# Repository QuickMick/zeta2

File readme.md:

streaming:
https://www.npmjs.com/package/h264-live-player
https://github.com/131/h264-live-player

old:https://www.npmjs.com/package/raspivid-stream

fan: 0.33 a
GY-88: 0.3 mA

pin input draw (zero position): 0.1 mA

kaufen:IRLML2502
schalter
lötsinn
kabel?
kondensator 47uf, 4.7uf 10uf
0.1uf
470uf
steckbrett

stepper: min 47uf

vllt au den:
IRF3708

crompzange

---------old----------

S8550 -< PNP
https://alltransistors.com/transistor.php?transistor=52917
Maximum Collector-Emitter Voltage |Vce|: 25 V
Maximum Emitter-Base Voltage |Veb|: 5 V
Maximum Collector Current |Ic max|: 0.5 A

S8050 -> TAKE DIS NPN
http://media.nkcelectronics.com/datasheet/s8050.pdf
700ma, 5v

2N5551 
300ma

tkae dis? 2N5401 --> is PNP
600ma

S9013 
0.5a

https://electronics.stackexchange.com/questions/95140/purpose-of-the-diode-and-capacitor-in-this-motor-circuit

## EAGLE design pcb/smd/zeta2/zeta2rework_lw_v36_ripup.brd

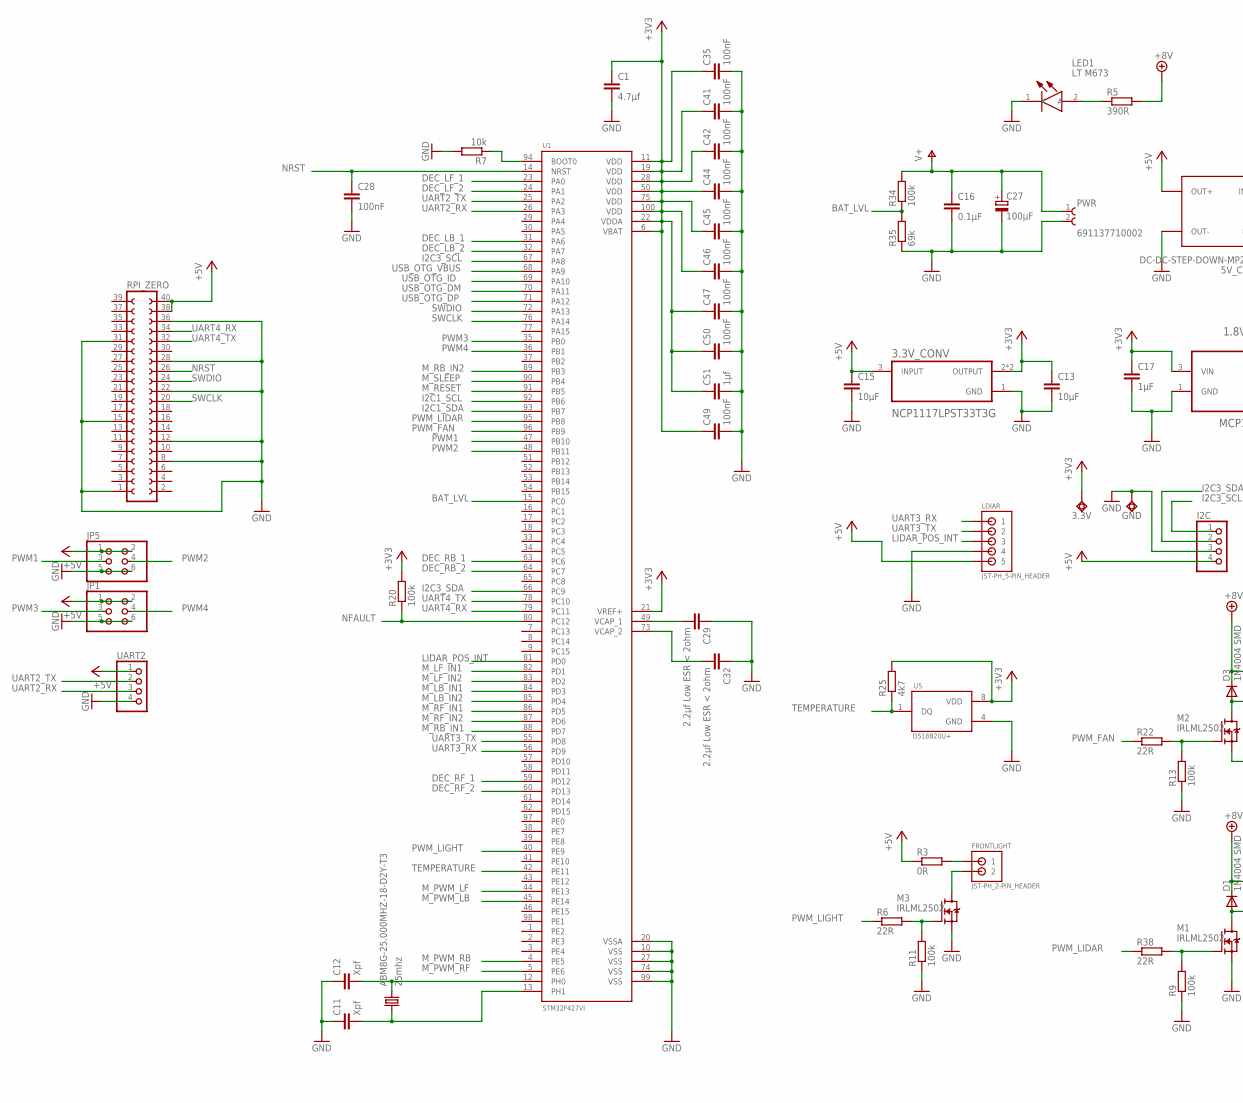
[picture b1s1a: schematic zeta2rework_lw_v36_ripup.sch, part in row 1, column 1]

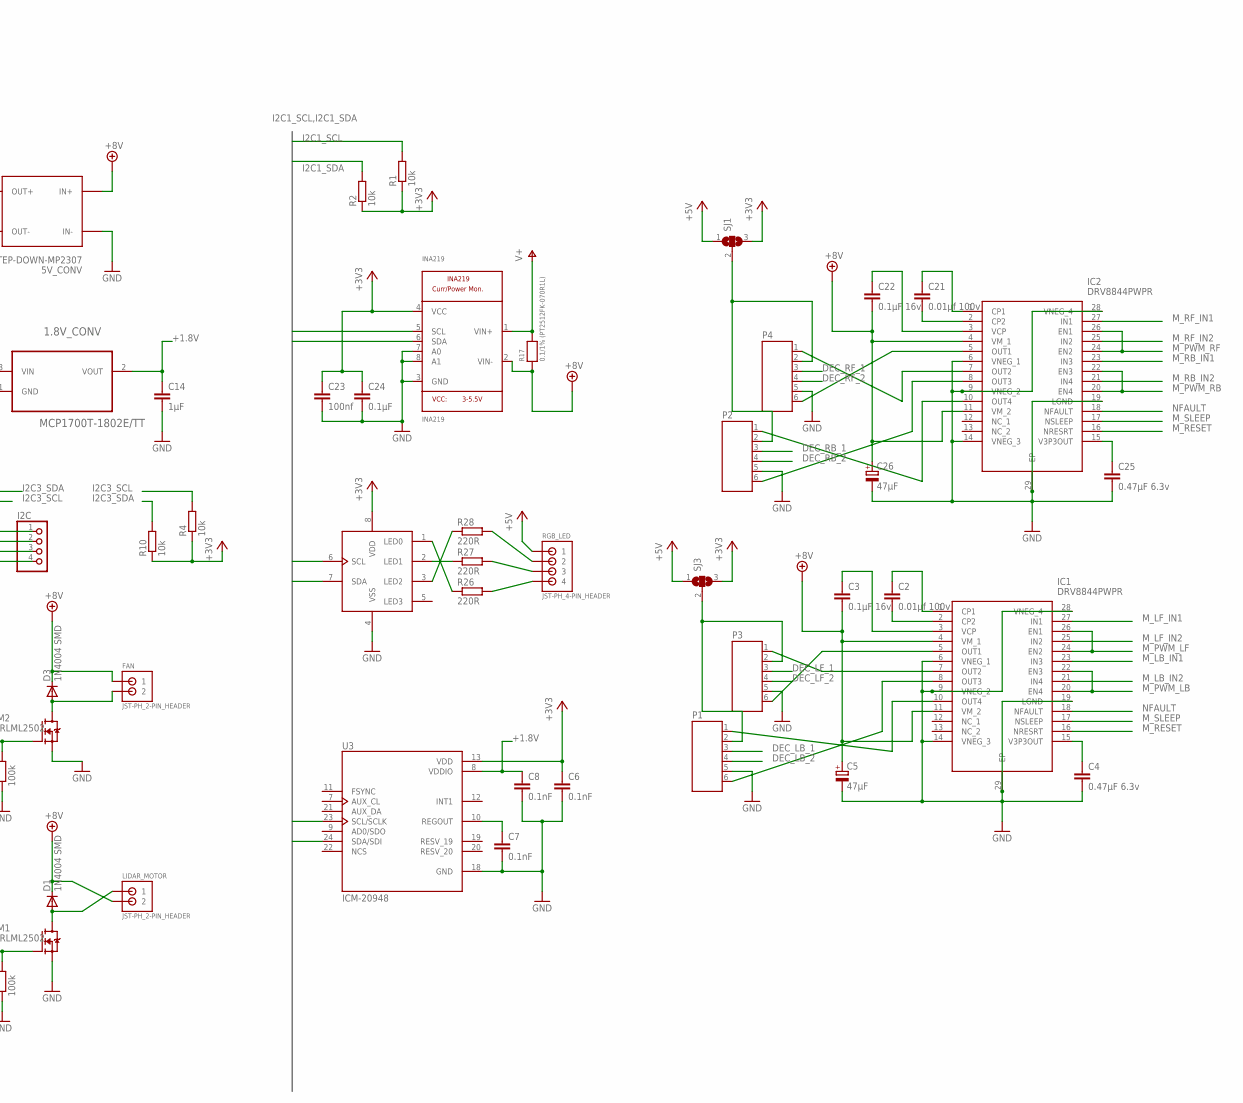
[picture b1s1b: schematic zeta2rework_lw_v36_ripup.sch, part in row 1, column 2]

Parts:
1.8V_CONV: MCP1700T-1802E/TT; SOT95P237X112-3N
3.3V: TPSQTP20R; TP20R
3.3V_CONV: NCP1117LPST33T3G; SOT230P700X175-4N
5V_CONV: DC-DC-STEP-DOWN-MP2307
ABM8G-25.000MHZ-18-D2Y-T3: 25mhz; 5.0X3.2_KX-9A
C1: 4.7µf; C0603
C2, C21: 0.01µf 100v; C0603
C3, C22: 0.1µF 16v; C0603
C4, C25: 0.47µF 6.3v; C0603
C5, C26: 47µF; UD-5X5,8_NICHICON
C6, C7, C8: 0.1nF; C0603
C11, C12: Xpf; C0603
C13, C15: 10µF; C1206
C14, C17: 1µF; C0603
C16, C24: 0.1µF; C0603
C23: 100nf; C0603
C27: 100µF; UD-5X5,8_NICHICON
C28, C35, C41, C42, C44, C45, C46, C47, C49, C50: 100nF; C0603
C29, C32: 2.2µf Low ESR < 2ohm; C1206
C51: 1µf; C0603
D1, D3: 1N4004 SMD; DO214AC
FAN: JST-PH_2-PIN_HEADER; JST_B2B-PH_HEADER
FRONTLIGHT: JST-PH_2-PIN_HEADER; JST_B2B-PH_HEADER
GND: TPSQTP20R; TP20R
I2C: PINHD-1X4; 1X04
IC1, IC2: DRV8844PWPR; SOP65P640X120-29N
INA219: INA219; SOT23-8
JP1, JP5: PINHD-2X3; 2X03
LDIAR: JST-PH_5-PIN_HEADER; JST_B5B-PH_HEADER
LED1: LT M673; LTM673-N1R2-25
LIDAR_MOTOR: JST-PH_2-PIN_HEADER; JST_B2B-PH_HEADER
M1, M2, M3: IRLML2502; SOT23
P1, P2, P3, P4: JST-PH6
PCA9533: PCA9533; SOIC8
PWR: 691137710002
R1, R2, R4, R7, R10: 10k; R0603
R3: 0R; R0603
R5: 390R; R0603
R6, R22, R38: 22R; R0603
R9, R11, R13, R20, R34: 100k; R0603
R17: 0.1/1% (PT2512FK-070R1L); 2512
R25: 4k7; R0603
R26, R27, R28: 220R; R0603
R35: 69k; R0603
RGB_LED: JST-PH_4-PIN_HEADER; JST_B4B-PH_HEADER
RPI_ZERO: FE20-2
SJ1, SJ3: SJ2W; SJ_2
U1: STM32F427VI; QFP50P1600X1600X160-100N
U3: ICM-20948; QFN40P300X300X105-25N
U5: DS18B20U+; SOP65P490X95-8N
UART2: PINHD-1X4; 1X04

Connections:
+1.8V: 1.8V_CONV.2 (VOUT), C8.1, C14.1, U3.8 (VDDIO)
+3V3: 1.8V_CONV.3 (VIN), 3.3V.TP, 3.3V_CONV.2 (OUTPUT), 3.3V_CONV.4 (OUTPUT), C1.1, C6.1, C13.1, C17.1, C23.1, C24.1, C35.1, C41.1, C42.1, C44.1, C45.1, C46.1, C47.1, C49.1, C50.1, C51.1, INA219.4 (VCC), PCA9533.8 (VDD), R1.1, R2.1, R4.1, R10.1, R20.2, R25.2, SJ1.3, SJ3.3, U1.6 (VBAT), U1.11 (VDD), U1.19 (VDD), U1.21 (VREF+), U1.22 (VDDA), U1.28 (VDD), U1.50 (VDD), U1.75 (VDD), U1.100 (VDD), U3.13 (VDD), U5.8 (VDD)
+5V: 3.3V_CONV.3 (INPUT), 5V_CONV.OUT+, C15.1, I2C.4, JP1.1, JP1.2, JP5.1, JP5.2, LDIAR.P5 (5), R3.1, RGB_LED.P1 (1), RPI_ZERO.38, RPI_ZERO.40, SJ1.1, SJ3.1, UART2.1
+8V: 5V_CONV.IN+, C3.2, C5.+, C22.2, C26.+, D1.C, D3.C, FAN.P1 (1), IC1.4 (VM_1), IC1.11 (VM_2), IC2.4 (VM_1), IC2.11 (VM_2), INA219.2 (VIN-), LIDAR_MOTOR.P2 (2), R5.2, R17.1
BAT_LVL: R34.1, R35.2, U1.15 (PC0)
DEC_LB_1: P1.3, U1.31 (PA6)
DEC_LB_2: P1.4, U1.32 (PA7)
DEC_LF_1: P3.3, U1.23 (PA0)
DEC_LF_2: P3.4, U1.24 (PA1)
DEC_RB_1: P2.3, U1.63 (PC6)
DEC_RB_2: P2.4, U1.64 (PC7)
DEC_RF_1: P4.3, U1.59 (PD12)
DEC_RF_2: P4.4, U1.60 (PD13)
GND: 1.8V_CONV.1 (GND), 3.3V_CONV.1 (GND), 5V_CONV.IN-, 5V_CONV.OUT-, C1.2, C4.2, C5.-, C6.2, C7.2, C8.2, C11.1, C12.1, C13.2, C14.2, C15.2, C16.2, C17.2, C23.2, C24.2, C25.2, C26.-, C27.-, C28.2, C29.1, C32.1, C35.2, C41.2, C42.2, C44.2, C45.2, C46.2, C47.2, C49.2, C50.2, C51.2, GND.TP, I2C.3, IC1.6 (VNEG_1), IC1.9 (VNEG_2), IC1.14 (VNEG_3), IC1.19 (LGND), IC1.28 (VNEG_4), IC1.29 (EP), IC2.6 (VNEG_1), IC2.9 (VNEG_2), IC2.14 (VNEG_3), IC2.19 (LGND), IC2.28 (VNEG_4), IC2.29 (EP), INA219.3 (GND), INA219.7 (A0), INA219.8 (A1), JP1.5, JP1.6, JP5.5, JP5.6, LDIAR.P4 (4), LED1.1 (K), M1.2 (S), M2.2 (S), M3.2 (S), P1.5, P2.5, P3.5, P4.5, PCA9533.4 (VSS), PWR.2, R7.2, R9.1, R11.1, R13.1, R35.1, RPI_ZERO.1, RPI_ZERO.8, RPI_ZERO.12, RPI_ZERO.15, RPI_ZERO.22, RPI_ZERO.28, RPI_ZERO.31, RPI_ZERO.36, U1.10 (VSS), U1.20 (VSSA), U1.27 (VSS), U1.74 (VSS), U1.99 (VSS), U3.18 (GND), U5.4 (GND), UART2.4
I2C1_SCL: INA219.5 (SCL), PCA9533.6 (SCL), R1.2, U1.92 (PB6), U3.23 (SCL/SCLK)
I2C1_SDA: INA219.6 (SDA), PCA9533.7 (SDA), R2.2, U1.93 (PB7), U3.24 (SDA/SDI)
I2C3_SCL: I2C.1, R4.2, U1.67 (PA8)
I2C3_SDA: I2C.2, R10.2, U1.66 (PC9)
LIDAR_POS_INT: LDIAR.P3 (3), U1.81 (PD0)
M_LB_IN1: IC1.23 (IN3), U1.84 (PD3)
M_LB_IN2: IC1.21 (IN4), U1.85 (PD4)
M_LF_IN1: IC1.27 (IN1), U1.82 (PD1)
M_LF_IN2: IC1.25 (IN2), U1.83 (PD2)
M_PWM_LB: IC1.20 (EN4), IC1.22 (EN3), U1.45 (PE14)
M_PWM_LF: IC1.24 (EN2), IC1.26 (EN1), U1.44 (PE13)
M_PWM_RB: IC2.20 (EN4), IC2.22 (EN3), U1.4 (PE5)
M_PWM_RF: IC2.24 (EN2), IC2.26 (EN1), U1.5 (PE6)
M_RB_IN1: IC2.23 (IN3), U1.88 (PD7)
M_RB_IN2: IC2.21 (IN4), U1.89 (PB3)
M_RESET: IC1.16 (NRESRT), IC2.16 (NRESRT), U1.91 (PB5)
M_RF_IN1: IC2.27 (IN1), U1.86 (PD5)
M_RF_IN2: IC2.25 (IN2), U1.87 (PD6)
M_SLEEP: IC1.17 (NSLEEP), IC2.17 (NSLEEP), U1.90 (PB4)
unnamed: C21.2, IC2.2 (CP2)
unnamed: C21.1, IC2.1 (CP1)
unnamed: C22.1, IC2.3 (VCP)
unnamed: IC2.10 (OUT4), P2.1
unnamed: FRONTLIGHT.P1 (1), R3.2
unnamed: LED1.2 (A), R5.1
unnamed: C7.1, U3.10 (REGOUT)
unnamed: FRONTLIGHT.P2 (2), M3.3 (D)
unnamed: M3.1 (G), R6.2, R11.2
unnamed: IC2.5 (OUT1), P4.6
unnamed: IC2.7 (OUT2), P4.1
unnamed: ABM8G-25.000MHZ-18-D2Y-T3.1, C11.2, U1.13 (PH1)
unnamed: IC1.5 (OUT1), P3.6
unnamed: R7.1, U1.94 (BOOT0)
unnamed: C2.2, IC1.2 (CP2)
unnamed: IC2.8 (OUT3), P2.6
unnamed: C2.1, IC1.1 (CP1)
unnamed: C3.1, IC1.3 (VCP)
unnamed: PCA9533.1 (LED0), R26.1
unnamed: PCA9533.2 (LED1), R27.1
unnamed: PCA9533.3 (LED2), R28.1
unnamed: C25.1, IC2.15 (V3P3OUT)
unnamed: IC1.7 (OUT2), P3.1
unnamed: IC1.8 (OUT3), P1.6
unnamed: C4.1, IC1.15 (V3P3OUT)
unnamed: IC1.10 (OUT4), P1.1
unnamed: R26.2, RGB_LED.P4 (4)
unnamed: P2.2, P4.2, SJ1.2
unnamed: R27.2, RGB_LED.P3 (3)
unnamed: R28.2, RGB_LED.P2 (2)
unnamed: C29.2, U1.49 (VCAP_1)
unnamed: M2.1 (G), R13.2, R22.2
unnamed: M1.1 (G), R9.2, R38.2
unnamed: D1.A, LIDAR_MOTOR.P1 (1), M1.3 (D)
unnamed: P1.2, P3.2, SJ3.2
unnamed: ABM8G-25.000MHZ-18-D2Y-T3.3 (2), C12.2, U1.12 (PH0)
unnamed: C32.2, U1.73 (VCAP_2)
unnamed: D3.A, FAN.P2 (2), M2.3 (D)
NFAULT: IC1.18 (NFAULT), IC2.18 (NFAULT), R20.1, U1.80 (PC12)
NRST: C28.1, RPI_ZERO.26, U1.14 (NRST)
PWM1: JP5.3, U1.47 (PB10)
PWM2: JP5.4, U1.48 (PB11)
PWM3: JP1.3, U1.35 (PB0)
PWM4: JP1.4, U1.36 (PB1)
PWM_FAN: R22.1, U1.96 (PB9)
PWM_LIDAR: R38.1, U1.95 (PB8)
PWM_LIGHT: R6.1, U1.40 (PE9)
SWCLK: RPI_ZERO.20, U1.76 (PA14)
SWDIO: RPI_ZERO.24, U1.72 (PA13)
TEMPERATURE: R25.1, U1.42 (PE11), U5.1 (DQ)
UART2_RX: U1.26 (PA3), UART2.3
UART2_TX: U1.25 (PA2), UART2.2
UART3_RX: LDIAR.P1 (1), U1.56 (PD9)
UART3_TX: LDIAR.P2 (2), U1.55 (PD8)
UART4_RX: RPI_ZERO.34, U1.79 (PC11)
UART4_TX: RPI_ZERO.32, U1.78 (PC10)
USB_OTG_DM: U1.70 (PA11)
USB_OTG_DP: U1.71 (PA12)
USB_OTG_ID: U1.69 (PA10)
USB_OTG_VBUS: U1.68 (PA9)
V+: C16.1, C27.+, INA219.1 (VIN+), PWR.1, R17.2, R34.2

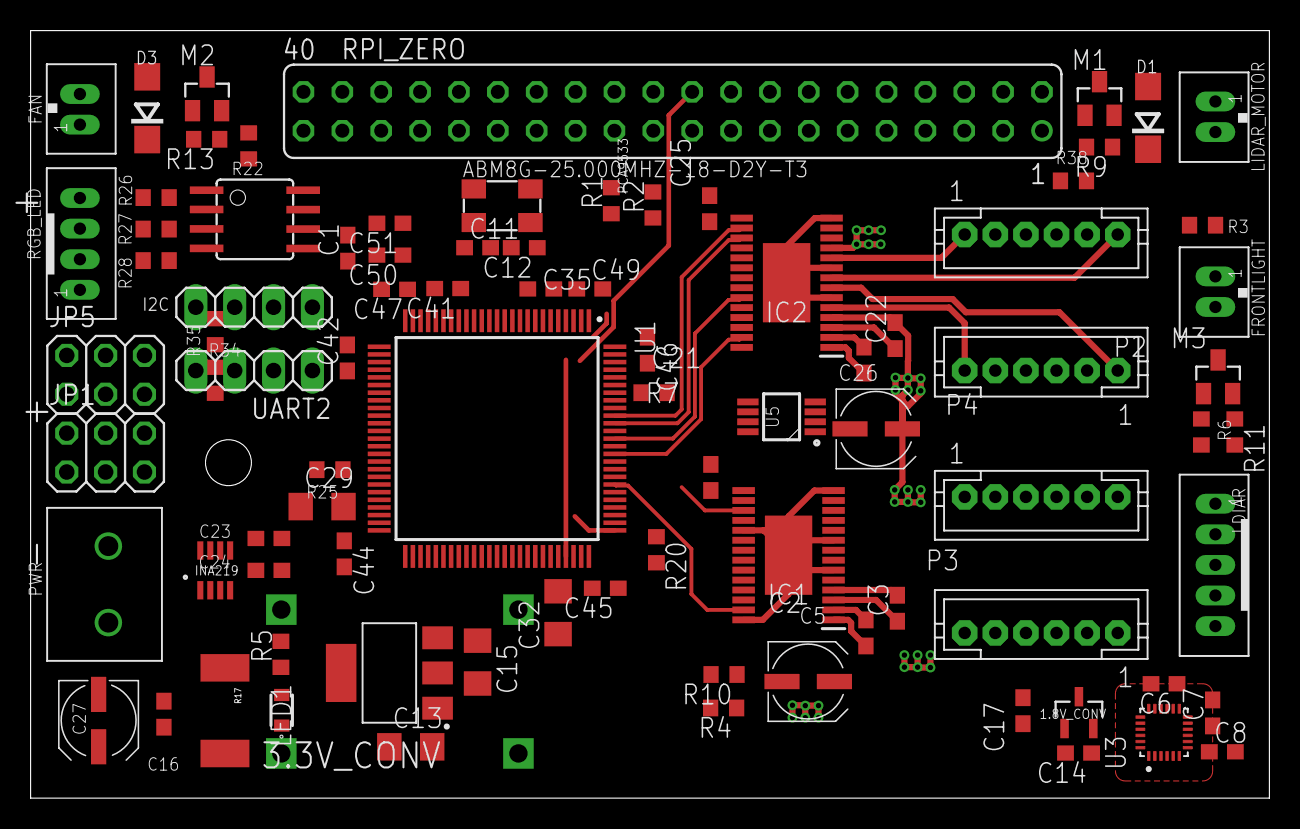
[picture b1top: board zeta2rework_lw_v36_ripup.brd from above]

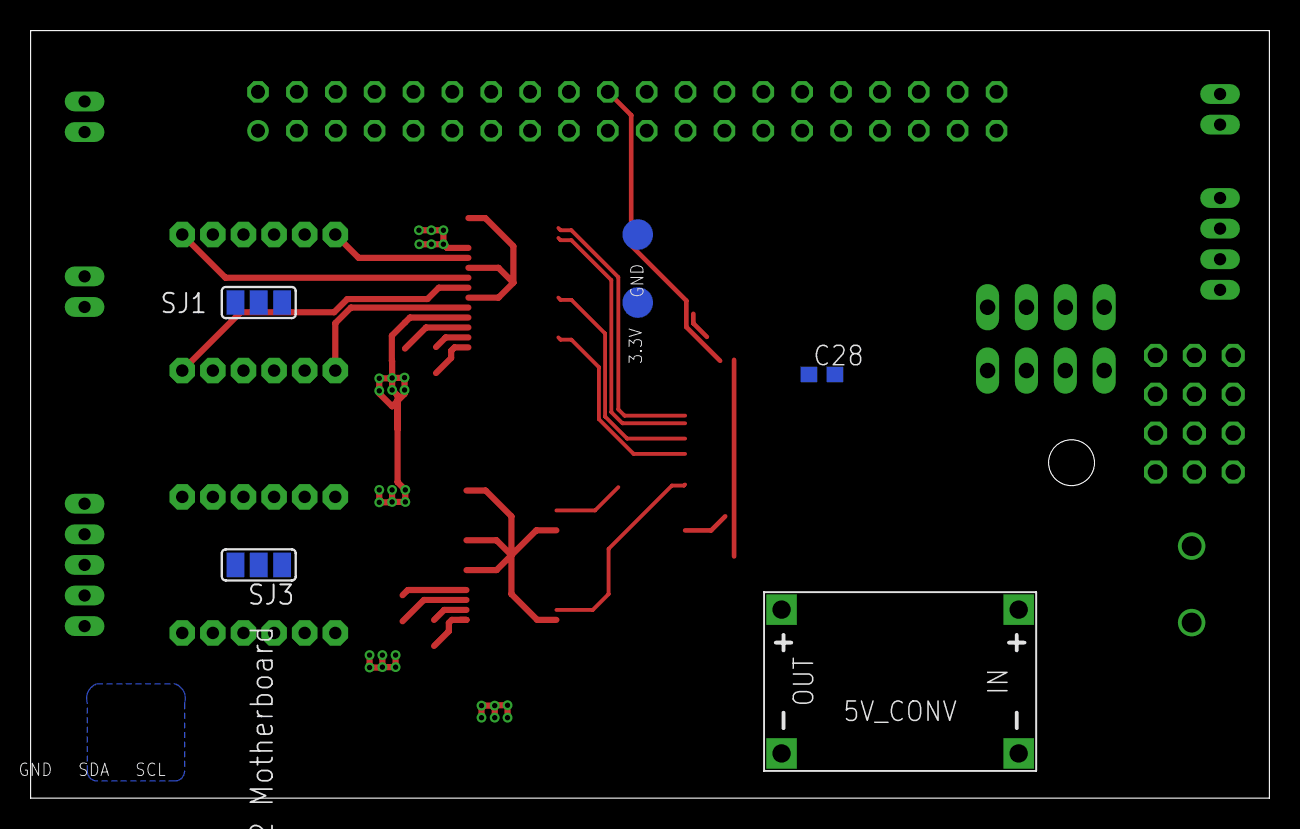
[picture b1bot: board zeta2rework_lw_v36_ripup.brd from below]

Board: 4 copper layers, 81.0 x 50.2 mm, 92 parts (6 on the bottom side), 90 nets.

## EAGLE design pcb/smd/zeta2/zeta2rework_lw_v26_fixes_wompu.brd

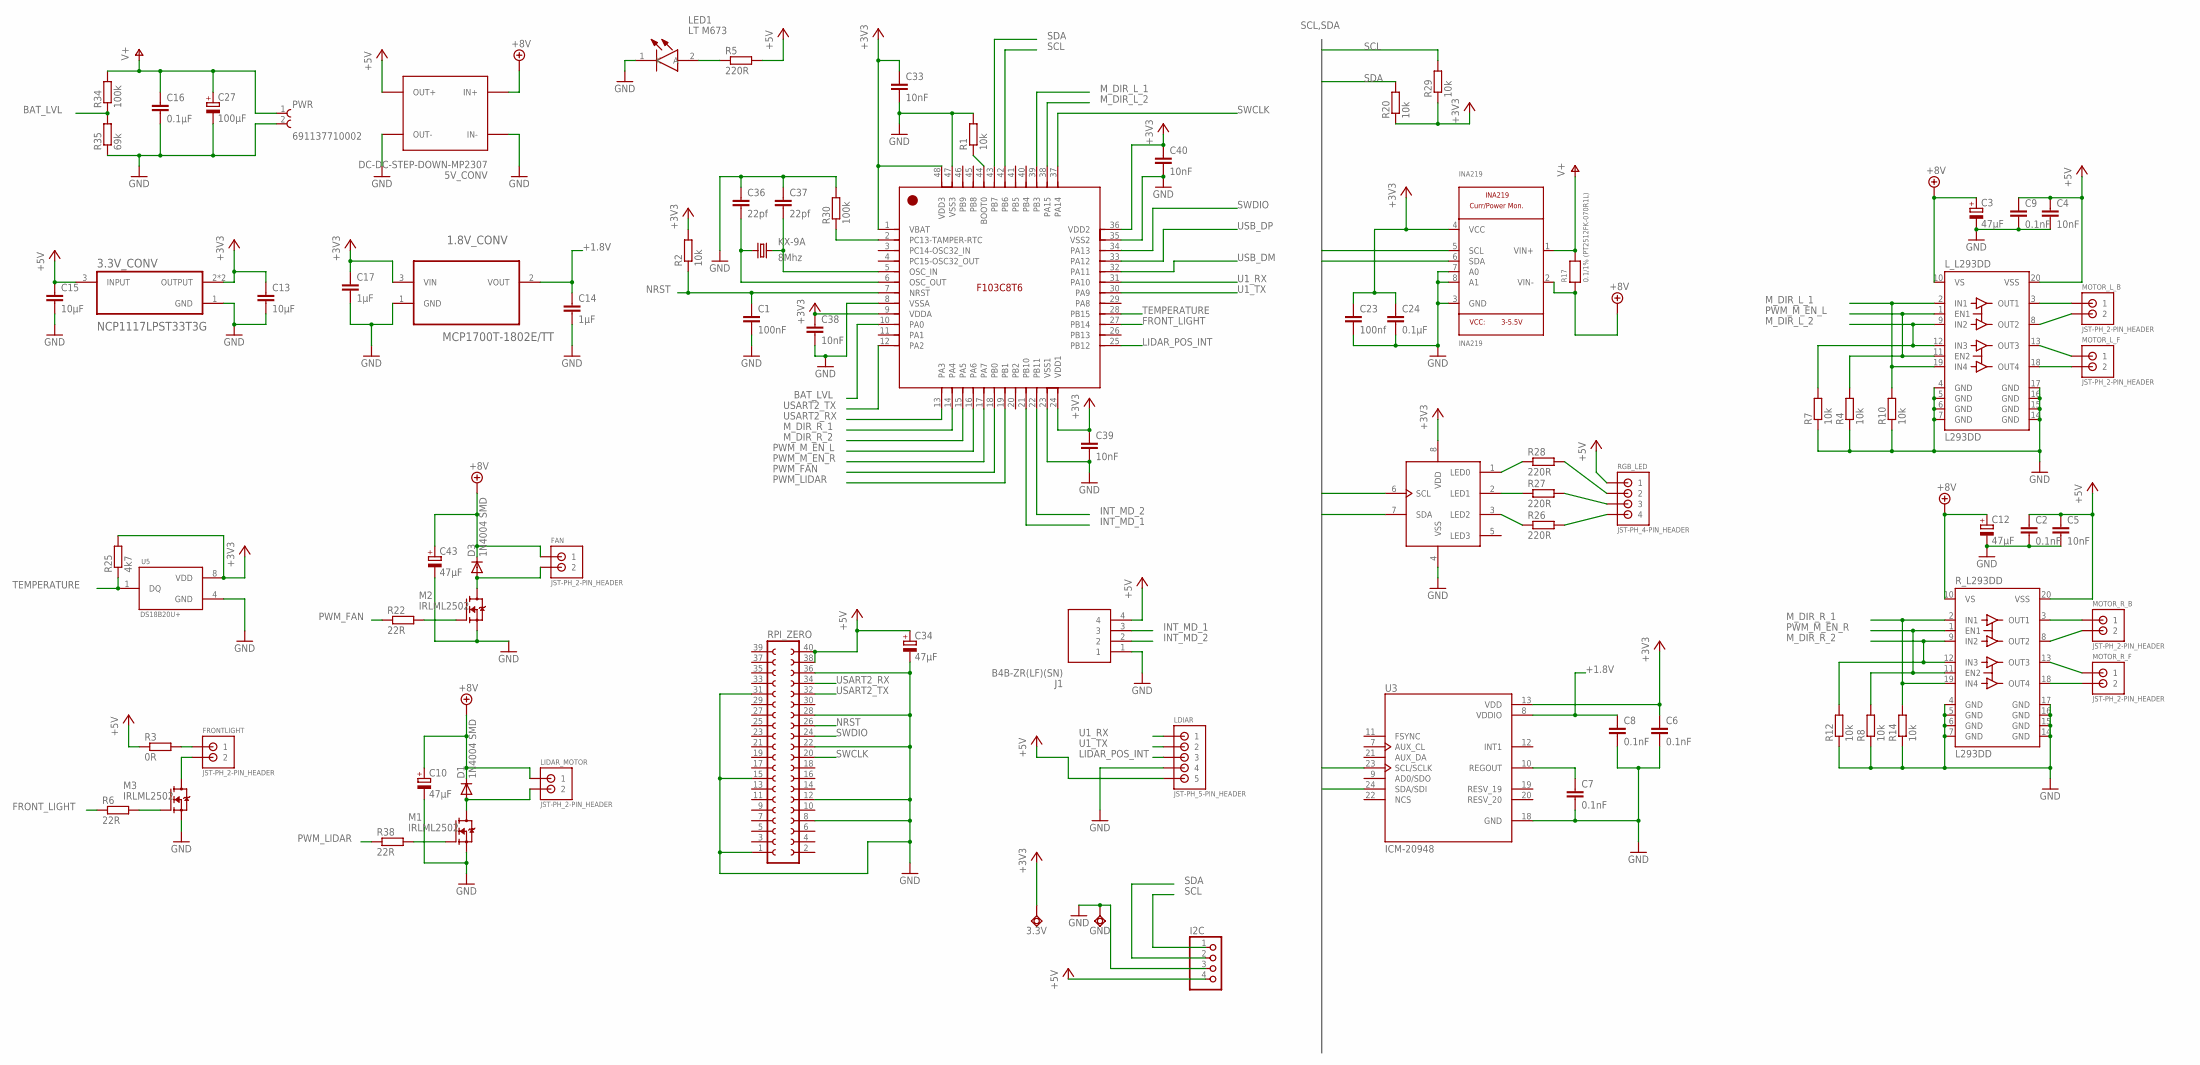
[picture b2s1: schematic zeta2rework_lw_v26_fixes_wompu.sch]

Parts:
1.8V_CONV: MCP1700T-1802E/TT; SOT95P237X112-3N
3.3V: TPSQTP20R; TP20R
3.3V_CONV: NCP1117LPST33T3G; SOT230P700X175-4N
5V_CONV: DC-DC-STEP-DOWN-MP2307
C1: 100nF; C1206
C2, C6, C7, C8, C9: 0.1nF; C1206
C3, C10, C12, C34, C43: 47µF; UD-5X5,8_NICHICON
C4, C5, C33, C38, C39, C40: 10nF; C1206
C13, C15: 10µF; C1206
C14, C17: 1µF; C1206
C16, C24: 0.1µF; C1206
C23: 100nf; C1206
C27: 100µF; UD-5X5,8_NICHICON
C36, C37: 22pf; C1206
D1, D3: 1N4004 SMD; DO214AC
FAN: JST-PH_2-PIN_HEADER; JST_B2B-PH_HEADER
FRONTLIGHT: JST-PH_2-PIN_HEADER; JST_B2B-PH_HEADER
GND: TPSQTP20R; TP20R
I2C: PINHD-1X4; 1X04
INA219: INA219; SOT23-8
J1: B4B-ZR(LF)(SN); SHDR4W50P0X150_1X4_750X350X450
KX-9A: 8Mhz; 5.0X3.2_KX-9A
LDIAR: JST-PH_5-PIN_HEADER; JST_B5B-PH_HEADER
LED1: LT M673; LTM673-N1R2-25
LIDAR_MOTOR: JST-PH_2-PIN_HEADER; JST_B2B-PH_HEADER
L_L293DD: L293DD; SO20
M1, M2, M3: IRLML2502; SOT23
MOTOR_L_B: JST-PH_2-PIN_HEADER; JST_B2B-PH_HEADER
MOTOR_L_F: JST-PH_2-PIN_HEADER; JST_B2B-PH_HEADER
MOTOR_R_B: JST-PH_2-PIN_HEADER; JST_B2B-PH_HEADER
MOTOR_R_F: JST-PH_2-PIN_HEADER; JST_B2B-PH_HEADER
PCA9533: PCA9533; SOIC8
PWR: 691137710002
R1, R2, R4, R7, R8, R10, R12, R14, R20, R29: 10k; R0603
R3: 0R; R0603
R5, R26, R27, R28: 220R; R0603
R6, R22, R38: 22R; R0603
R17: 0.1/1% (PT2512FK-070R1L); 2512
R25: 4k7; R0603
R30, R34: 100k; R0603
R35: 69k; R0603
RGB_LED: JST-PH_4-PIN_HEADER; JST_B4B-PH_HEADER
RPI_ZERO: FE20-2
R_L293DD: L293DD; SO20
STM32F103CB: STM32F103CB; LQFP48_7X7MM_0.5MMPP
U3: ICM-20948; QFN40P300X300X105-25N
U5: DS18B20U+; SOP65P490X95-8N

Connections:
+1.8V: 1.8V_CONV.2 (VOUT), C8.1, C14.1, U3.8 (VDDIO)
+3V3: 1.8V_CONV.3 (VIN), 3.3V.TP, 3.3V_CONV.2 (OUTPUT), 3.3V_CONV.4 (OUTPUT), C6.1, C13.1, C17.1, C23.1, C24.1, C33.1, C38.1, C39.1, C40.1, INA219.4 (VCC), PCA9533.8 (VDD), R2.2, R20.1, R25.2, R29.1, STM32F103CB.1 (VBAT), STM32F103CB.9 (VDDA), STM32F103CB.24 (VDD1), STM32F103CB.36 (VDD2), STM32F103CB.48 (VDD3), U3.13 (VDD), U5.8 (VDD)
+5V: 3.3V_CONV.3 (INPUT), 5V_CONV.OUT+, C2.1, C4.1, C5.1, C9.1, C15.1, C34.+, I2C.4, J1.4, LDIAR.P5 (5), L_L293DD.20 (VSS), R3.1, R5.2, RGB_LED.P1 (1), RPI_ZERO.38, RPI_ZERO.40, R_L293DD.20 (VSS)
+8V: 5V_CONV.IN+, C3.+, C10.+, C12.+, C43.+, D1.C, D3.C, FAN.P1 (1), INA219.2 (VIN-), LIDAR_MOTOR.P1 (1), L_L293DD.10 (VS), R17.1, R_L293DD.10 (VS)
BAT_LVL: R34.1, R35.2, STM32F103CB.10 (PA0)
FRONT_LIGHT: R6.1, STM32F103CB.27 (PB14)
GND: 1.8V_CONV.1 (GND), 3.3V_CONV.1 (GND), 5V_CONV.IN-, 5V_CONV.OUT-, C1.2, C2.2, C3.-, C4.2, C5.2, C6.2, C7.2, C8.2, C9.2, C10.-, C12.-, C13.2, C14.2, C15.2, C16.2, C17.2, C23.2, C24.2, C27.-, C33.2, C34.-, C36.1, C37.1, C38.2, C39.2, C40.2, C43.-, GND.TP, I2C.3, INA219.3 (GND), INA219.7 (A0), INA219.8 (A1), J1.1, LDIAR.P4 (4), LED1.1 (K), L_L293DD.4 (GND), L_L293DD.5 (GND), L_L293DD.6 (GND), L_L293DD.7 (GND), L_L293DD.14 (GND), L_L293DD.15 (GND), L_L293DD.16 (GND), L_L293DD.17 (GND), M1.2 (S), M2.2 (S), M3.2 (S), PCA9533.4 (VSS), PWR.2, R1.2, R4.1, R7.1, R8.1, R10.1, R12.1, R14.1, R30.2, R35.1, RPI_ZERO.1, RPI_ZERO.8, RPI_ZERO.12, RPI_ZERO.15, RPI_ZERO.22, RPI_ZERO.28, RPI_ZERO.31, RPI_ZERO.36, R_L293DD.4 (GND), R_L293DD.5 (GND), R_L293DD.6 (GND), R_L293DD.7 (GND), R_L293DD.14 (GND), R_L293DD.15 (GND), R_L293DD.16 (GND), R_L293DD.17 (GND), STM32F103CB.8 (VSSA), STM32F103CB.23 (VSS1), STM32F103CB.35 (VSS2), STM32F103CB.47 (VSS3), U3.18 (GND), U5.4 (GND)
INT_MD_1: J1.3, STM32F103CB.21 (PB10)
INT_MD_2: J1.2, STM32F103CB.22 (PB11)
LIDAR_POS_INT: LDIAR.P3 (3), STM32F103CB.25 (PB12)
M_DIR_L_1: L_L293DD.2 (IN1), L_L293DD.19 (IN4), R10.2, STM32F103CB.39 (PB3)
M_DIR_L_2: L_L293DD.9 (IN2), L_L293DD.12 (IN3), R7.2, STM32F103CB.38 (PA15)
M_DIR_R_1: R14.2, R_L293DD.2 (IN1), R_L293DD.19 (IN4), STM32F103CB.14 (PA4)
M_DIR_R_2: R12.2, R_L293DD.9 (IN2), R_L293DD.12 (IN3), STM32F103CB.15 (PA5)
unnamed: MOTOR_R_B.P2 (2), R_L293DD.8 (OUT2)
unnamed: MOTOR_R_F.P2 (2), R_L293DD.18 (OUT4)
unnamed: MOTOR_R_F.P1 (1), R_L293DD.13 (OUT3)
unnamed: L_L293DD.18 (OUT4), MOTOR_L_F.P2 (2)
unnamed: R1.1, STM32F103CB.44 (BOOT0)
unnamed: FRONTLIGHT.P1 (1), R3.2
unnamed: LED1.2 (A), R5.1
unnamed: C7.1, U3.10 (REGOUT)
unnamed: FRONTLIGHT.P2 (2), M3.3 (D)
unnamed: M3.1 (G), R6.2
unnamed: L_L293DD.13 (OUT3), MOTOR_L_F.P1 (1)
unnamed: L_L293DD.8 (OUT2), MOTOR_L_B.P2 (2)
unnamed: L_L293DD.3 (OUT1), MOTOR_L_B.P1 (1)
unnamed: PCA9533.3 (LED2), R26.1
unnamed: PCA9533.2 (LED1), R27.1
unnamed: PCA9533.1 (LED0), R28.1
unnamed: MOTOR_R_B.P1 (1), R_L293DD.3 (OUT1)
unnamed: R26.2, RGB_LED.P4 (4)
unnamed: R27.2, RGB_LED.P3 (3)
unnamed: R28.2, RGB_LED.P2 (2)
unnamed: M2.1 (G), R22.2
unnamed: M1.1 (G), R38.2
unnamed: D1.A, LIDAR_MOTOR.P2 (2), M1.3 (D)
unnamed: C36.2, KX-9A.1, STM32F103CB.6 (OSC_OUT)
unnamed: C37.2, KX-9A.3 (2), STM32F103CB.5 (OSC_IN)
unnamed: R30.1, STM32F103CB.2 (PC13-TAMPER-RTC)
unnamed: D3.A, FAN.P2 (2), M2.3 (D)
NRST: C1.1, R2.1, RPI_ZERO.26, STM32F103CB.7 (NRST)
PWM_FAN: R22.1, STM32F103CB.18 (PB0)
PWM_LIDAR: R38.1, STM32F103CB.19 (PB1)
PWM_M_EN_L: L_L293DD.1 (EN1), L_L293DD.11 (EN2), R4.2, STM32F103CB.16 (PA6)
PWM_M_EN_R: R8.2, R_L293DD.1 (EN1), R_L293DD.11 (EN2), STM32F103CB.17 (PA7)
SCL: I2C.1, INA219.5 (SCL), PCA9533.6 (SCL), R29.2, STM32F103CB.42 (PB6), U3.23 (SCL/SCLK)
SDA: I2C.2, INA219.6 (SDA), PCA9533.7 (SDA), R20.2, STM32F103CB.43 (PB7), U3.24 (SDA/SDI)
SWCLK: RPI_ZERO.20, STM32F103CB.37 (PA14)
SWDIO: RPI_ZERO.24, STM32F103CB.34 (PA13)
TEMPERATURE: R25.1, STM32F103CB.28 (PB15), U5.1 (DQ)
U1_RX: LDIAR.P1 (1), STM32F103CB.31 (PA10)
U1_TX: LDIAR.P2 (2), STM32F103CB.30 (PA9)
USART2_RX: RPI_ZERO.34, STM32F103CB.13 (PA3)
USART2_TX: RPI_ZERO.32, STM32F103CB.12 (PA2)
USB_DM: STM32F103CB.32 (PA11)
USB_DP: STM32F103CB.33 (PA12)
V+: C16.1, C27.+, INA219.1 (VIN+), PWR.1, R17.2, R34.2

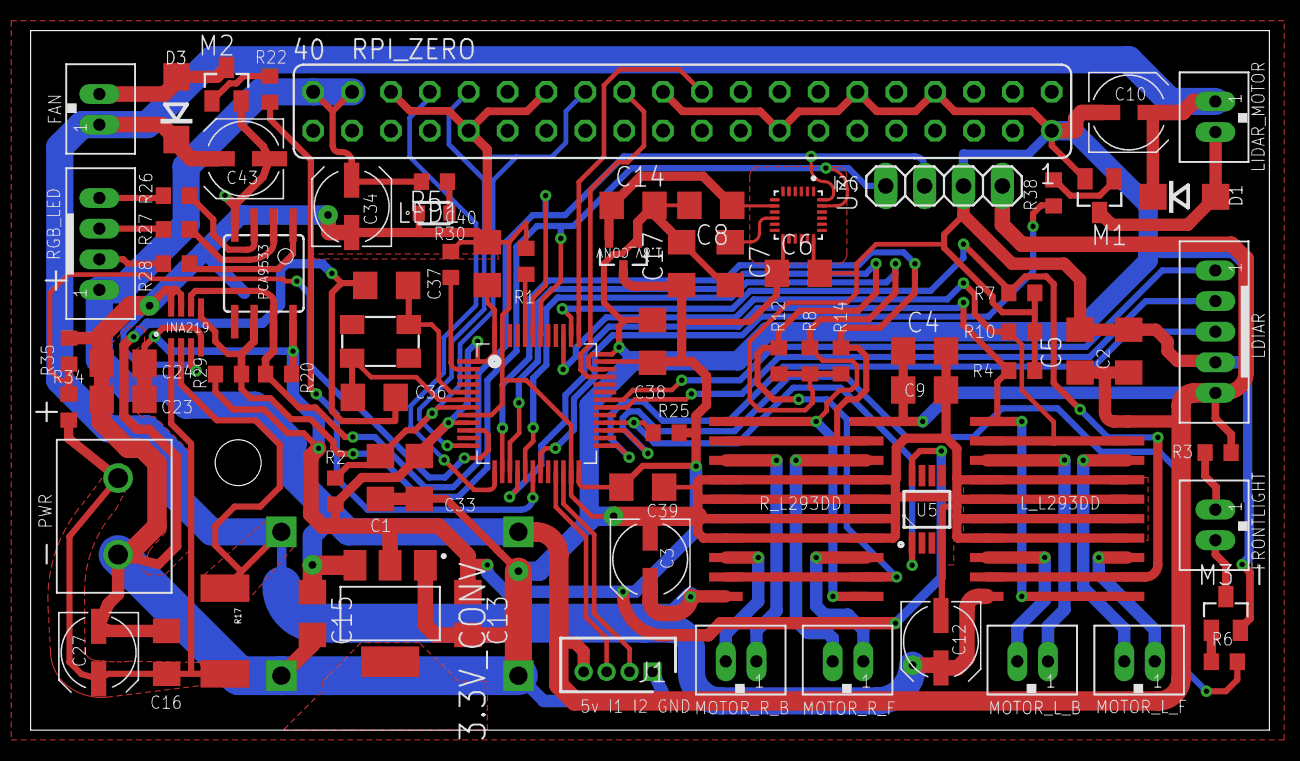
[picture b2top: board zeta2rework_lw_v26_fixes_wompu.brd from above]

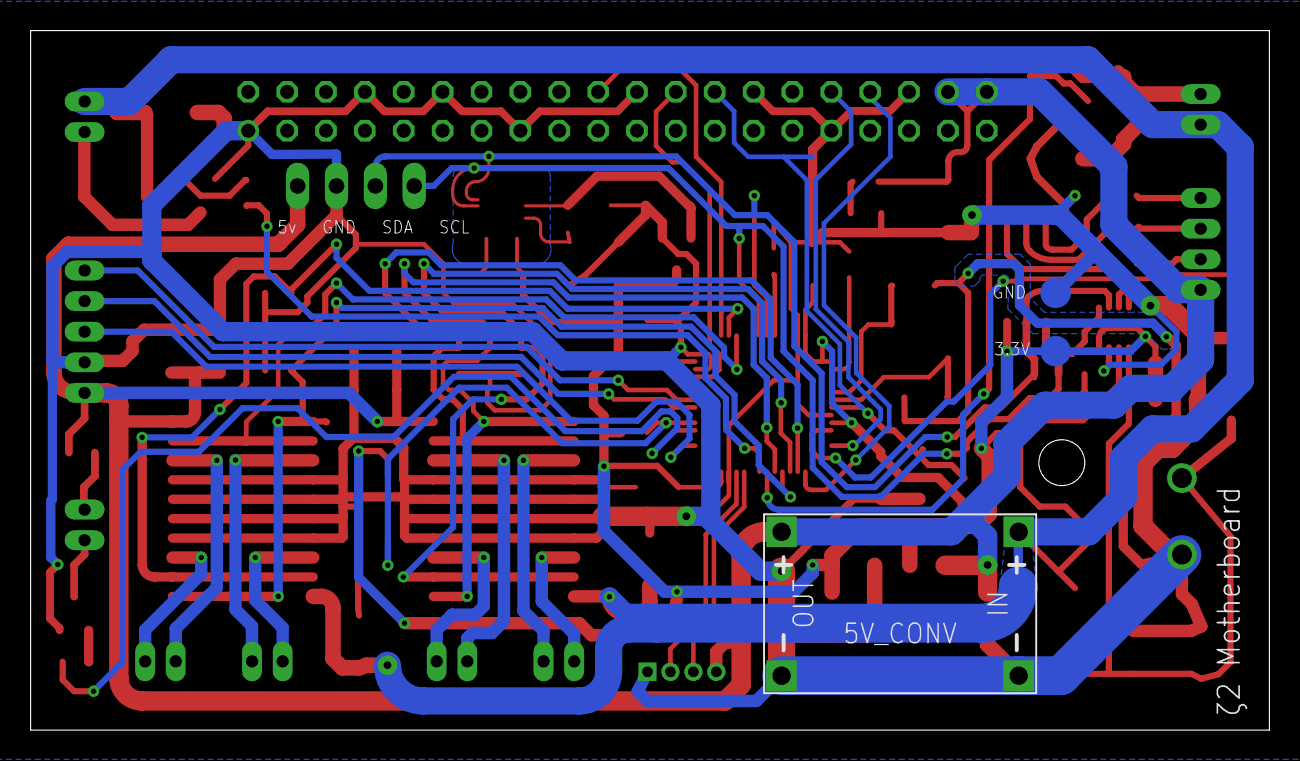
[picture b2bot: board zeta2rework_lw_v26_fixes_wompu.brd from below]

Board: 2 copper layers, 81.0 x 45.7 mm, 82 parts (3 on the bottom side), 56 nets.

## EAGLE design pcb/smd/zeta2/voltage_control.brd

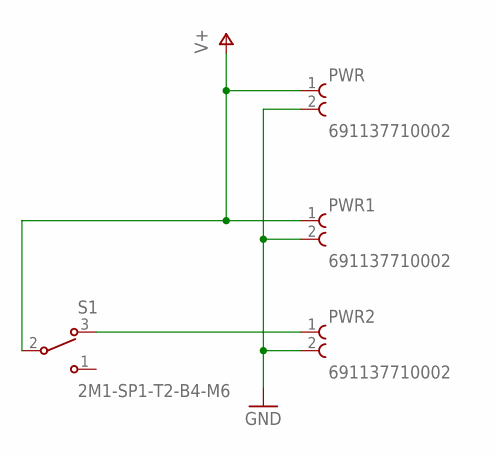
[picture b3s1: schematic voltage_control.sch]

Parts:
PWR, PWR1, PWR2: 691137710002
S1: 2M1-SP1-T2-B4-M6

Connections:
GND: PWR.2, PWR1.2, PWR2.2
unnamed: PWR2.1, S1.3 (O)
V+: PWR.1, PWR1.1, S1.2

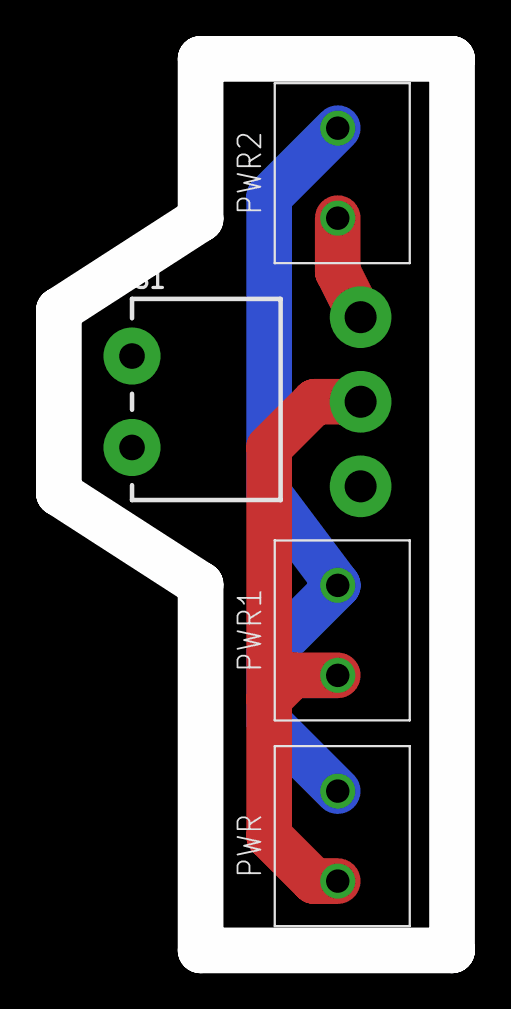
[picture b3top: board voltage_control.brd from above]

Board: 2 copper layers, 21.8 x 49.5 mm, 4 parts (0 on the bottom side), 3 nets.

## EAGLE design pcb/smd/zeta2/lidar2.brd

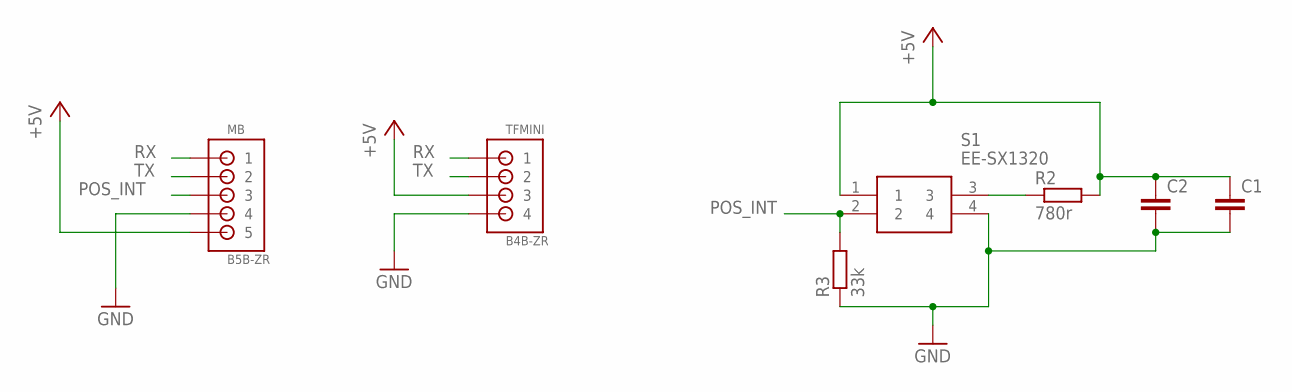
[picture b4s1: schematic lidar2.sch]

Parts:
C1: C-EUC1206; C1206
C2: C-EUC0805; C0805
MB: B5B-ZR
R2: 780r; R0603
R3: 33k; R0603
S1: EE-SX1320
TFMINI: B4B-ZR

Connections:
+5V: C1.1, C2.1, MB.5, R2.2, S1.1, TFMINI.3
GND: C1.2, C2.2, MB.4, R3.1, S1.4, TFMINI.4
unnamed: R2.1, S1.3
POS_INT: MB.3, R3.2, S1.2
RX: MB.1, TFMINI.1
TX: MB.2, TFMINI.2

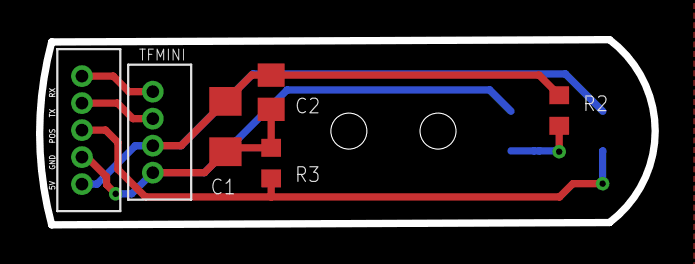
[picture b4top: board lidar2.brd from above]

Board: 2 copper layers, 34.2 x 10.3 mm, 7 parts (1 on the bottom side), 6 nets.

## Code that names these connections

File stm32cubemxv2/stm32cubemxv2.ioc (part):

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Mcu.Name=STM32F427V(G-I)Tx
Mcu.Package=LQFP100
Mcu.UserName=STM32F427VITx
PA0/WKUP.GPIOParameters=GPIO_PuPd,GPIO_Label
PA0/WKUP.GPIO_Label=DEC_LF_1
PA0/WKUP.GPIO_PuPd=GPIO_PULLUP
PA0/WKUP.Signal=S_TIM2_CH1_ETR
PA1.GPIOParameters=GPIO_PuPd,GPIO_Label
PA1.GPIO_Label=DEC_LF_2
PA1.GPIO_PuPd=GPIO_PULLUP
PA1.Signal=S_TIM2_CH2
PA10.Mode=OTG/Dual_Role_Device
PA10.Signal=USB_OTG_FS_ID
PA11.Mode=OTG/Dual_Role_Device
PA11.Signal=USB_OTG_FS_DM
PA12.Mode=OTG/Dual_Role_Device
PA12.Signal=USB_OTG_FS_DP
PA13.Mode=Serial_Wire
PA13.Signal=SYS_JTMS-SWDIO
PA14.Mode=Serial_Wire
PA14.Signal=SYS_JTCK-SWCLK
PA2.Mode=Asynchronous
PA2.Signal=USART2_TX
PA3.Mode=Asynchronous
PA3.Signal=USART2_RX
PA6.GPIOParameters=GPIO_PuPd,GPIO_Label
PA6.GPIO_Label=DEC_LB_1
PA6.GPIO_PuPd=GPIO_PULLUP
PA6.Signal=S_TIM3_CH1
PA7.GPIOParameters=GPIO_PuPd,GPIO_Label
PA7.GPIO_Label=DEC_LB_2
PA7.GPIO_PuPd=GPIO_PULLUP
PA7.Signal=S_TIM3_CH2
PA8.Mode=I2C
PA8.Signal=I2C3_SCL
PA9.Mode=Activate_VBUS
PA9.Signal=USB_OTG_FS_VBUS
PB0.GPIOParameters=GPIO_Label
PB0.GPIO_Label=PWM3
PB0.Signal=S_TIM3_CH3
PB1.GPIOParameters=GPIO_Label
PB1.GPIO_Label=PWM4
PB1.Signal=S_TIM3_CH4
PB10.GPIOParameters=GPIO_Label
PB10.GPIO_Label=PWM1
PB10.Signal=S_TIM2_CH3
PB11.GPIOParameters=GPIO_Label
PB11.GPIO_Label=PWM2
PB11.Signal=S_TIM2_CH4
PB3.GPIOParameters=GPIO_Label
PB3.GPIO_Label=M_RB_IN2
PB3.Signal=GPIO_Output
PB4.GPIOParameters=GPIO_Label
PB4.GPIO_Label=M_SLEEP
PB4.Signal=GPIO_Output
PB5.GPIOParameters=GPIO_Label
PB5.GPIO_Label=M_RESET
PB5.Signal=GPIO_Output
PB6.Mode=I2C
PB6.Signal=I2C1_SCL
PB7.Mode=I2C
PB7.Signal=I2C1_SDA
PB8.GPIOParameters=GPIO_Label
PB8.GPIO_Label=PWM_LIDAR
PB8.Signal=S_TIM10_CH1
PB9.GPIOParameters=GPIO_Label
PB9.GPIO_Label=PWM_FAN
PB9.Signal=S_TIM11_CH1
PC0.GPIOParameters=GPIO_Label
PC0.GPIO_Label=BAT_LVL
PC0.Signal=ADCx_IN10
PC10.Mode=Asynchronous
PC10.Signal=UART4_TX
PC11.Mode=Asynchronous
PC11.Signal=UART4_RX
PC12.GPIOParameters=GPIO_Label
PC12.GPIO_Label=NFAULT
PC12.Signal=GPXTI12
PC6.GPIOParameters=GPIO_PuPd,GPIO_Label
PC6.GPIO_Label=DEC_RB_1
PC6.GPIO_PuPd=GPIO_PULLUP
PC6.Signal=S_TIM8_CH1
PC7.GPIOParameters=GPIO_PuPd,GPIO_Label
PC7.GPIO_Label=DEC_RB_2
PC7.GPIO_PuPd=GPIO_PULLUP
PC7.Signal=S_TIM8_CH2
PC9.Mode=I2C
PC9.Signal=I2C3_SDA
PD0.GPIOParameters=GPIO_PuPd,GPIO_Label
PD0.GPIO_Label=LIDAR_POS_INT
PD0.GPIO_PuPd=GPIO_PULLDOWN
PD0.Signal=GPXTI0
PD1.GPIOParameters=GPIO_Label
PD1.GPIO_Label=M_LF_IN1
PD1.Signal=GPIO_Output
PD12.GPIOParameters=GPIO_PuPd,GPIO_Label
PD12.GPIO_Label=DEC_RF_1
PD12.GPIO_PuPd=GPIO_PULLUP
PD12.Signal=S_TIM4_CH1
PD13.GPIOParameters=GPIO_PuPd,GPIO_Label
PD13.GPIO_Label=DEC_RF_2
PD13.GPIO_PuPd=GPIO_PULLUP
PD13.Signal=S_TIM4_CH2
PD2.GPIOParameters=GPIO_Label
PD2.GPIO_Label=M_LF_IN2
PD2.Signal=GPIO_Output
PD3.GPIOParameters=GPIO_Label
PD3.GPIO_Label=M_LB_IN1
PD3.Signal=GPIO_Output
PD4.GPIOParameters=GPIO_Label
PD4.GPIO_Label=M_LB_IN2
PD4.Signal=GPIO_Output
PD5.GPIOParameters=GPIO_Label
PD5.GPIO_Label=M_RF_IN1
PD5.Signal=GPIO_Output
PD6.GPIOParameters=GPIO_Label
PD6.GPIO_Label=M_RF_IN2
PD6.Signal=GPIO_Output
PD7.GPIOParameters=GPIO_Label
PD7.GPIO_Label=M_RB_IN1
PD7.Signal=GPIO_Output
PD8.Mode=Asynchronous
PD8.Signal=USART3_TX
PD9.Mode=Asynchronous
PD9.Signal=USART3_RX
PE11.GPIOParameters=GPIO_Label
PE11.GPIO_Label=TEMPERATURE
PE11.Signal=GPIO_Input
PE13.GPIOParameters=GPIO_Label
PE13.GPIO_Label=M_PWM_LF
PE13.Signal=S_TIM1_CH3
PE14.GPIOParameters=GPIO_Label
PE14.GPIO_Label=M_PWM_LB
PE14.Signal=S_TIM1_CH4
PE5.GPIOParameters=GPIO_Label
PE5.GPIO_Label=M_PWM_RF
PE5.Signal=S_TIM9_CH1
PE6.GPIOParameters=GPIO_Label
PE6.GPIO_Label=M_PWM_RB
PE6.Signal=S_TIM9_CH2
PE9.GPIOParameters=GPIO_Label
PE9.GPIO_Label=PWM_LIGHT
PE9.Signal=S_TIM1_CH1
PH0/OSC_IN.Signal=RCC_OSC_IN
PH1/OSC_OUT.Signal=RCC_OSC_OUT
RCC.HSE_VALUE=25000000
RCC.SYSCLKFreq_VALUE=16000000
board=custom

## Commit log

2018-06-12 added libs
2018-06-12 motor stuff
2018-06-12 more motor
2018-06-13 added fan, ino in testing mode
2018-06-14 added temperature sensor
2018-06-14 added first draft of rpi server
2018-06-16 added pcb
2018-06-17 new pcb version
2018-06-17 pcb update
2018-06-17 changed pcb
2018-07-03 matched pins to new layout
2018-07-10 addded eagle files
2018-07-24 added i2c device
2018-07-26 worked on pcb, fixed stm32 layout
2018-07-26 added temperature sensor to l239d, heatplate missing
2018-07-27 worked on pcb layout -piheader wrong
2018-08-01 added hall effect sensor
2018-08-02 worked on layout
2018-08-05 adde capicator for mp6500
2019-02-05 added new pcb version
2019-02-10 finished pcb
2019-02-10 small changes
2019-02-10 using ph for leds again
2019-02-10 fixed power supply
2019-02-10 added extensionn pins
2019-02-12 removed l293d transistors
2019-02-17 added new lidar pcb, added new version of mainboard, added stls for mb and lidar pcb
2019-03-05 working on fixes of pcb
2019-03-11 version 3 of pcb should be finihsed now
2019-03-12 moved pwr in, added smd LED
2019-03-15 changed to new parts
2019-03-18 using stm32f4, fixed pin settings, added cubemx
2019-03-19 added usb
2019-03-23 working on new pcb layout
2019-03-26 progress on traces
2019-03-27 connected power supply

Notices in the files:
parts and their libraries:
switch-ck: Copyright (C) 2011, Bob Starr
diy-modules: Released under the Creative Commons Attribution 4.0 International License: http://creativecommons.org/licenses/by/4.0
crystal-geyer_V1_0: Copyright: Geyer-Electronic
